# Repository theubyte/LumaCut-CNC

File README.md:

Screenshots von 684590c3a18e5fe78f427af118488d666ded8a3e (main)

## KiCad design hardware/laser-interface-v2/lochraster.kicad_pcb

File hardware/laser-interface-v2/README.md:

# LumaCut Laser-Interface V2

Eine Platine für Laserversorgung (Relais G5LE-1 am SKR-FAN1, Sicherung 2 A T)
und Laser-PWM (PA1 → Optokoppler SFH618A/PC817 → geregelte 5 V vom 7805 (Lochraster: LM317T mit 220/680 Ω) →
gelber Laserdraht, 2,2 kΩ nach Masse). SKR-Seite und Laser-Seite haben keine
gemeinsame Leiterbahn.

| Datei | Inhalt |
|---|---|
| `schaltplan.svg/.png` | Schaltplan |
| `build_board.py` → `laser_interface_v2.kicad_pcb` | Platine zum Fertigen (90 × 64 mm, 2 Lagen, nur bedrahtet) |
| `LumaCut-Laser-IF-V2-gerber.zip` | Gerber + Bohrdaten für JLCPCB (Upload, kein Stencil nötig) |
| `render_top.png`, `render_bottom.png` | Vorschau Platine |
| `build_perfboard.py` → `lochraster.kicad_pcb` | gleiche Schaltung auf Lochraster 7 × 9 cm, U2 = LM317T aus der Gasheizungsplatine (03.11.) |
| `bauplan_lochraster.png` (`bauplan.html`) | Bauplan Lochraster: beide Seiten, Löcher, Drähte |
| `lochraster_liste.txt` | Bauteil- und Drahtliste aus dem Skript |

Skripte laufen mit KiCads Python (KiCad 10):
`"%LOCALAPPDATA%/Programs/KiCad/10.0/bin/python.exe" build_board.py`,
danach DRC/Gerber mit `kicad-cli pcb drc|export gerbers|export drill`.
DRC der Platine: 0 Verstöße, 0 offene Verbindungen (03.11.2026).

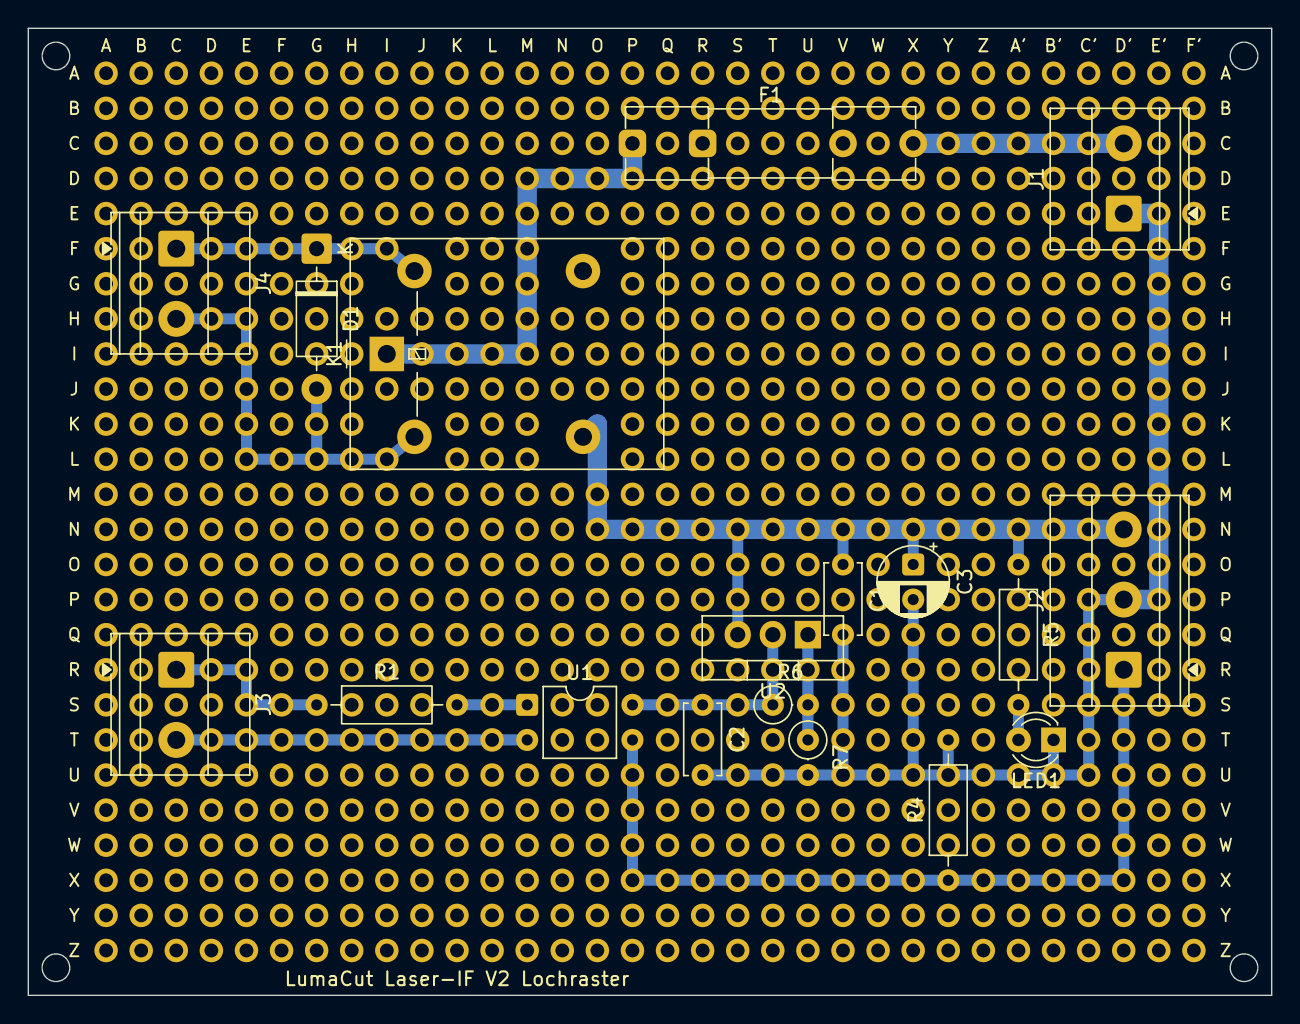
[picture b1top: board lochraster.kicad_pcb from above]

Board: 2 copper layers, 90.0 x 70.0 mm, 19 parts (0 on the bottom side), 13 nets.

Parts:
C1, C2: 100n; C_Disc_D5.0mm_W2.5mm_P5.00mm
C3: 10u; CP_Radial_D5.0mm_P2.50mm
D1: 1N4007; D_DO-41_SOD81_P10.16mm_Horizontal
F1: 2A T; Fuseholder_Clip-5x20mm_Littelfuse_111_Inline_P20.00x5.00mm_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
J1: Netzteil; TerminalBlock_Phoenix_MKDS-1,5-2_1x02_P5.00mm_Horizontal
J2: Laser; TerminalBlock_Phoenix_MKDS-1,5-3_1x03_P5.00mm_Horizontal
J3: SKR BL_Touch; TerminalBlock_Phoenix_MKDS-1,5-2_1x02_P5.00mm_Horizontal
J4: SKR FAN1; TerminalBlock_Phoenix_MKDS-1,5-2_1x02_P5.00mm_Horizontal
K1: G5LE-1 24VDC; Relay_SPDT_Omron-G5LE-1
LED1: LED; LED_D3.0mm
LOCH: (no value)
R1: 680; R_Axial_DIN0207_L6.3mm_D2.5mm_P10.16mm_Horizontal
R4: 2k2; R_Axial_DIN0207_L6.3mm_D2.5mm_P10.16mm_Horizontal
R5: 4k7; R_Axial_DIN0207_L6.3mm_D2.5mm_P10.16mm_Horizontal
R6: 220; R_Axial_DIN0207_L6.3mm_D2.5mm_P2.54mm_Vertical
R7: 680; R_Axial_DIN0207_L6.3mm_D2.5mm_P2.54mm_Vertical
U1: SFH618A/PC817; DIP-4_W7.62mm
U2: LM317T; TO-220-3_Vertical

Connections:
+5V: C2.1, R6.1, U1.4, U2.2
+24V_F: F1.1, K1.1
+24V_IN: F1.2, J1.2
+24V_SW: C1.1, C3.1, J2.3, K1.3, R5.1, U2.3
ADJ: R6.2, R7.1, U2.1
FAN+: D1.1, J4.1, K1.5
FAN-: D1.2, J4.2, K1.2
GND: C1.2, C2.2, C3.2, J1.1, J2.2, LED1.1, R4.2, R7.2
GND_SKR: J3.2, U1.2
LED_A: LED1.2, R5.2
OPTO_A: R1.2, U1.1
PA1: J3.1, R1.1
PWM: J2.1, R4.1, U1.3
